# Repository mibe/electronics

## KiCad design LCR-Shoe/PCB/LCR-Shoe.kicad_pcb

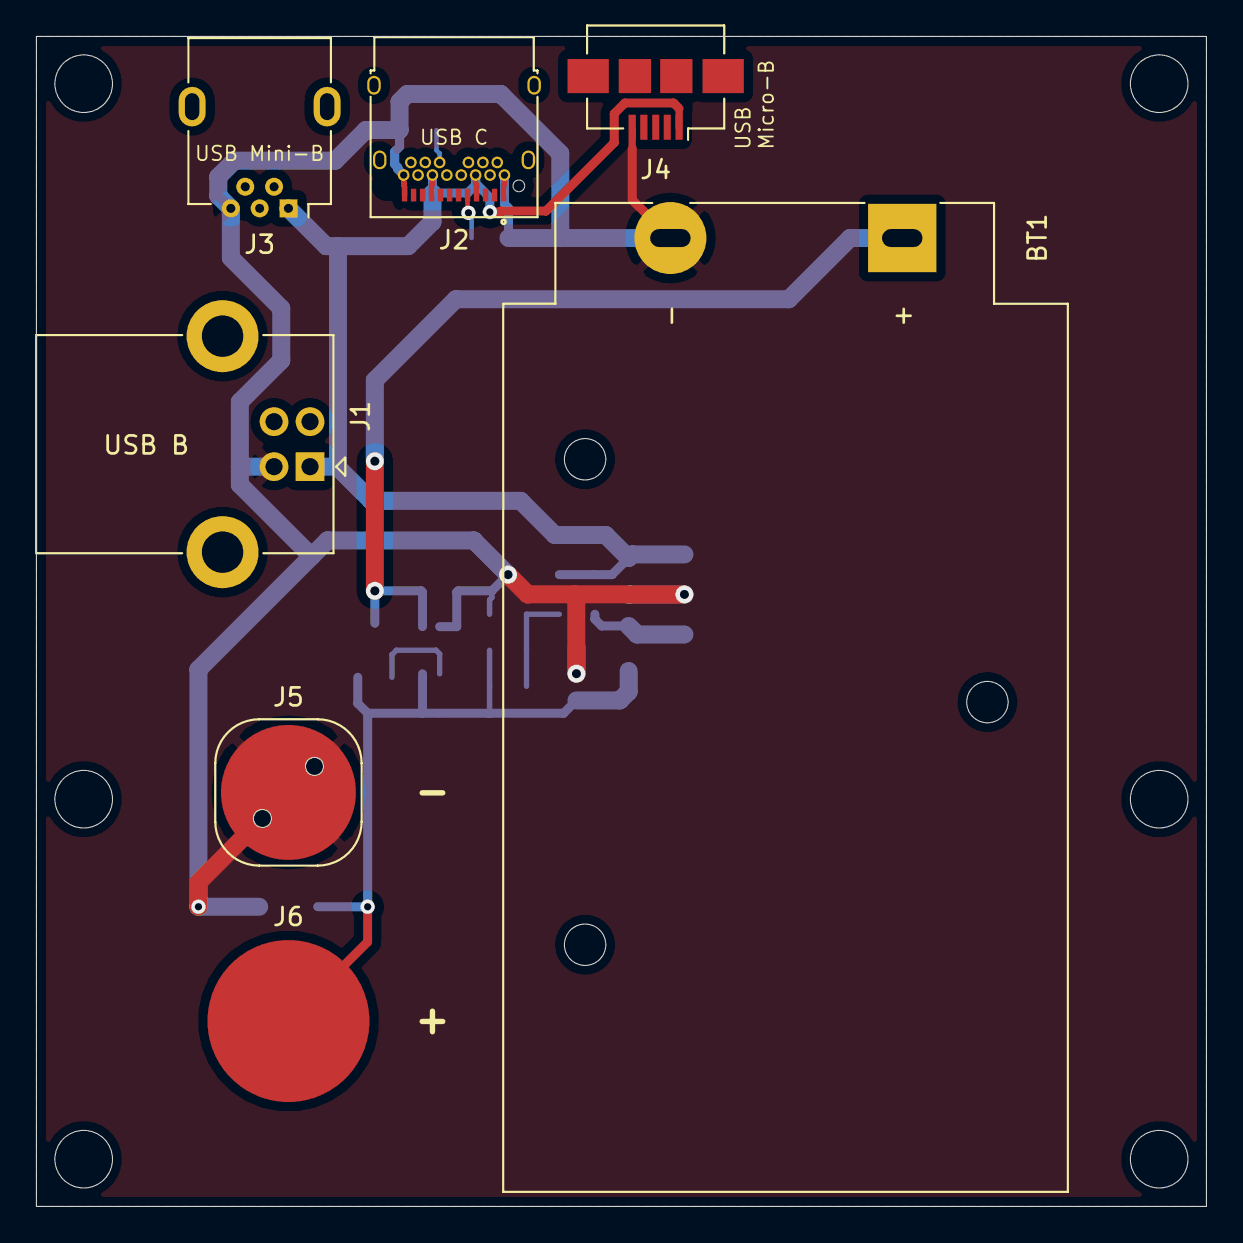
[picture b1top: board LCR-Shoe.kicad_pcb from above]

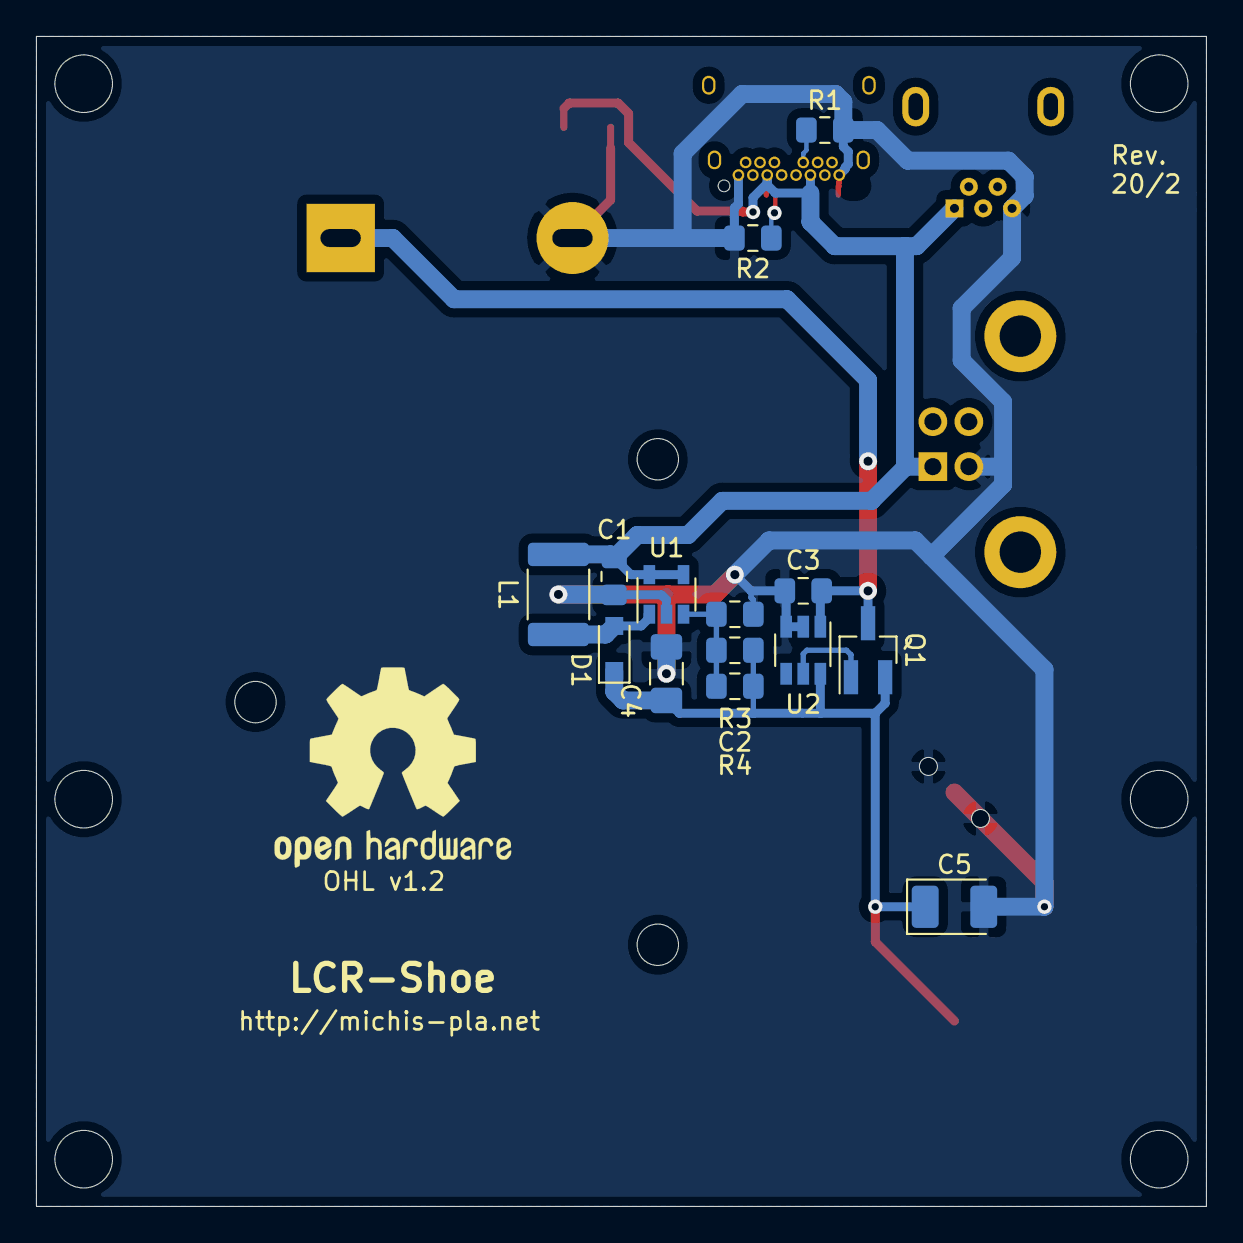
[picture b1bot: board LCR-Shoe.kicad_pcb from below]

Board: 2 copper layers, 65.0 x 65.0 mm, 28 parts (15 on the bottom side), 10 nets.

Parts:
BT1: Battery_Cell; BatteryHolder_MPD_BA9VPC_1xPP3
C1: 2.2µ; C_0805_2012Metric_Pad1.15x1.40mm_HandSolder
C2: 270p; C_0805_2012Metric_Pad1.15x1.40mm_HandSolder
C3: 100n; C_0805_2012Metric_Pad1.15x1.40mm_HandSolder
C4: 4.7µ; C_1206_3216Metric_Pad1.42x1.75mm_HandSolder
C5: 2.2µ; CP_EIA-3528-12_Kemet-T_Pad1.50x2.35mm_HandSolder
D1: NSR0320MW2T1G; D_SOD-323_HandSoldering
H1, H2, H3, H4, H5, H6: MountingHole; MountingHole_3.2mm_M3
J1: USB_B; USB_B_Lumberg_2411_02
J2: USB_C_Receptacle; USB_C_Receptacle_Bellwether_80211-x92
J3: USB_B_Mini; USB_Mini-B_Reichelt_BWM
J4: USB_B_Micro; USB_Micro-B_Amphenol_10104110
J5: Conn_01x01_Female; Keystone_269
J6: Conn_01x01_Male; Keystone_261
L1: LQH43MN100K03L; L_1812_4532Metric_Pad1.30x3.40mm_HandSolder
NT1: Net-Tie_2; NetTie-2_SMD_Pad0.5mm
Q1: IRLML6402PbF; SOT-23_Handsoldering
R1, R2: 5.1k; R_0805_2012Metric_Pad1.15x1.40mm_HandSolder
R3: 15k; R_0805_2012Metric_Pad1.15x1.40mm_HandSolder
R4: 110k; R_0805_2012Metric_Pad1.15x1.40mm_HandSolder
U1: LM2731YMF; SOT-23-5
U2: LTC4412xS6; TSOT-23-6

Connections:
+5V: C1.1, J1.1, J2.A4, J2.A9, J2.B4, J2.B9, J3.1, J4.1, L1.1, U1.4, U1.5
+9V: BT1.1, C3.1, Q1.3, U2.1
+10V: C2.2, C4.1, D1.1, NT1.1, R4.2
/FB: C2.1, R3.1, R4.1, U1.3
/G: Q1.1, U2.5
/SW: D1.2, L1.2, U1.1
/USB_C-CC1: J2.A5, R2.1
/USB_C-CC2: J2.B5, R1.1
GND: BT1.2, C1.2, C3.2, C4.2, C5.2, J1.4, J2.A1, J2.A12, J2.B1, J2.B12, J3.5, J4.5, J5.1, R1.2, R2.2, R3.2, U1.2, U2.2, U2.3
VCC: C5.1, J6.1, NT1.2, Q1.2, U2.6

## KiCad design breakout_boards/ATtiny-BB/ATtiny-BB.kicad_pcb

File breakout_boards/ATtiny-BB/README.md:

# ATtiny-BB
A small breakout-board for mounting an 8-pin Atmel ATtiny onto a breadboard.

# BOM
- 8-pin DIP socket (U1)
- 10-pin pin strip (J1, J2, J3)
- 1x jumper (on J3)
- Tactile switch C&K KMR2 with grounding pin (SW1)
- 100 nF 0805 capacitor (C1)
- 330 Ω 0805 resistor (R1)

# Design & building notes
* The resistor R1 limits the current, if the reset switch is pressed by accident when the RESET pin is used as an I/O pin.
* J3 is intended for measuring the current consumption of the system. Hence J3 is shorted with a jumper when not used.
* The standoff (```standoff.STL```) is mounted on the mounting hole by using a M3 screw.

# License
(C) 2018 Michael Bemmerl

[CERN OHL 1.2 License](https://www.ohwr.org/documents/294)

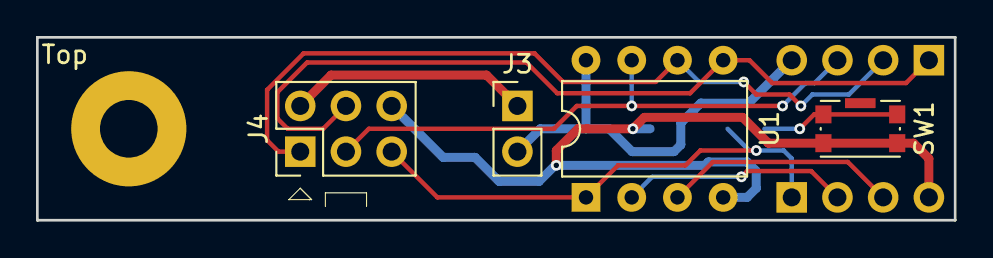
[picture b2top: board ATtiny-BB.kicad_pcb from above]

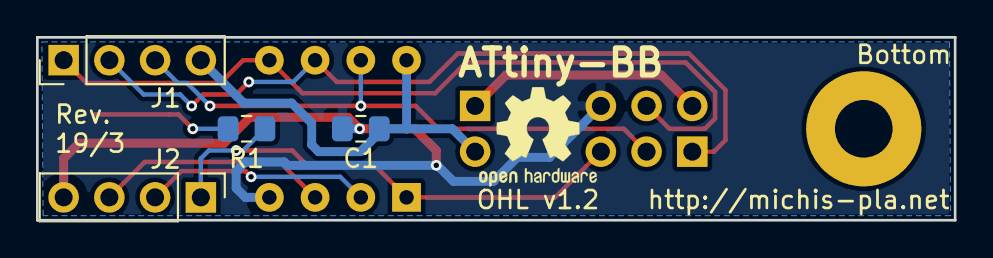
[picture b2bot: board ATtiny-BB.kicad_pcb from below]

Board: 2 copper layers, 51.0 x 10.2 mm, 8 parts (4 on the bottom side), 10 nets.

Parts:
C1: 100n; C_0805_2012Metric_Pad1.15x1.40mm_HandSolder
J1, J2: Conn_01x04; PinHeader_1x04_P2.54mm_Vertical
J3: Conn_01x02; PinHeader_1x02_P2.54mm_Vertical
J4: AVR-ISP-6; PinHeader_2x03_P2.54mm_Vertical
R1: 330; R_0805_2012Metric_Pad1.15x1.40mm_HandSolder
SW1: SW_Push; SW_Push_1P1T_NO_CK_KMR2_GNDPad
U1: ATTINY45-20PU; DIP-8_W7.62mm

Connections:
/GND: C1.2, J2.4, J4.6, SW1.2, U1.4
/PB0: J1.1, J4.4, U1.5
/PB1: J1.2, J4.1, U1.6
/PB2: J1.3, J4.3, U1.7
/PB3: J2.2, U1.2
/PB4: J2.3, U1.3
/PB5: J2.1, J4.5, R1.1, U1.1
/VCC: C1.1, J1.4, J3.2, U1.8
/VCC_in: J3.1, J4.2
unnamed: R1.2, SW1.1

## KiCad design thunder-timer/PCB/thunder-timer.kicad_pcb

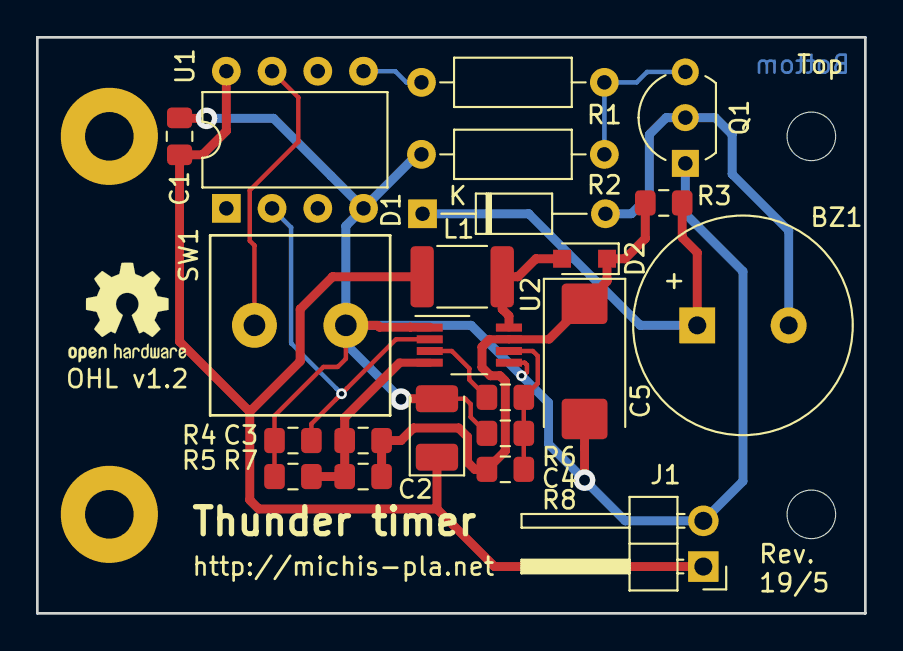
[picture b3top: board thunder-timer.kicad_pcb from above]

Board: 2 copper layers, 46.0 x 32.0 mm, 22 parts (0 on the bottom side), 13 nets.

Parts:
BZ1: Buzzer; Buzzer_12x9.5RM5
C1, C4: 100n; C_0805_2012Metric_Pad1.15x1.40mm_HandSolder
C2: 22µ; CP_EIA-3528-21_Kemet-B_Pad1.50x2.35mm_HandSolder
C3: 39p; C_0805_2012Metric_Pad1.15x1.40mm_HandSolder
C5: 68µ; CP_EIA-7343-31_Kemet-D_Pad2.25x2.55mm_HandSolder
D1: 1N4148; D_DO-35_SOD27_P10.16mm_Horizontal
D2: NSR0320MW2T1G; D_SOD-323_HandSoldering
J1: Conn_01x02; PinHeader_1x02_P2.54mm_Horizontal
L1: 6µ8; L_1812_4532Metric_Pad1.30x3.40mm_HandSolder
Q1: 2PC945; TO-92L_Inline_Wide
R1: 6.8k; R_Axial_DIN0207_L6.3mm_D2.5mm_P10.16mm_Horizontal
R2: 33k; R_Axial_DIN0207_L6.3mm_D2.5mm_P10.16mm_Horizontal
R3: 82; R_0805_2012Metric_Pad1.15x1.40mm_HandSolder
R4: 100k; R_0805_2012Metric_Pad1.15x1.40mm_HandSolder
R5: 50k; R_0805_2012Metric_Pad1.15x1.40mm_HandSolder
R6: 200k; R_0805_2012Metric_Pad1.15x1.40mm_HandSolder
R7: 150k; R_0805_2012Metric_Pad1.15x1.40mm_HandSolder
R8: 500; R_0805_2012Metric_Pad1.15x1.40mm_HandSolder
SW1: SW_Push; SW_Push_10mm
U1: ATTINY85-20PU; DIP-8_W7.62mm
U2: LM2621; VSSOP-8_3.0x3.0mm_P0.65mm

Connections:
+5V: C3.1, C5.1, D2.1, R3.1, R7.2, R8.1, U2.7
/DCDC-VCC: C4.1, R6.1, R8.2, U2.6
/FB: C3.2, R5.2, R7.1, U2.4
BUZ_PWM: R1.2, U1.5
DCDC-PWR: R4.1, U1.2, U2.2
GND: C1.2, C2.2, C4.2, C5.2, J1.2, Q1.1, R2.2, R4.2, R5.1, SW1.1, U1.4, U2.1, U2.5
unnamed: BZ1.1, D1.1, R3.2
unnamed: BZ1.2, D1.2, Q1.2
unnamed: D2.2, L1.2, U2.8
unnamed: Q1.3, R1.1, R2.1
unnamed: R6.2, U2.3
unnamed: SW1.2, U1.7
VCC: C1.1, C2.1, J1.1, L1.1, U1.8

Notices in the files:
LCR-Shoe/PCB/LCR-Shoe.kicad_pcb:
Open Hardware: CERN OHL v1.2
